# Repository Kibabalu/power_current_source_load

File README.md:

# power_current_source_load

power current source and load

A KiCad project.

The project consists of three PCBs: A general purpose power supply PCB, the control/supervise PCB and the main power PCB.

The power supply PCB gives a clean and stable +/- 15 V output voltage from a 'dirty' switching-mode power supply at its input. In detail it has the functions:
- inverse-polarity protection
- common mode disturbance filtering 
- low pass filtering with fg approx. 3 kHz (Pi-filter)
- low pass filtering with fg approx. 1.5 Hz (RC-Filter with capacitance multiplier)
- Voltage control of +/- 15 V, I_max approx. 1.5 A

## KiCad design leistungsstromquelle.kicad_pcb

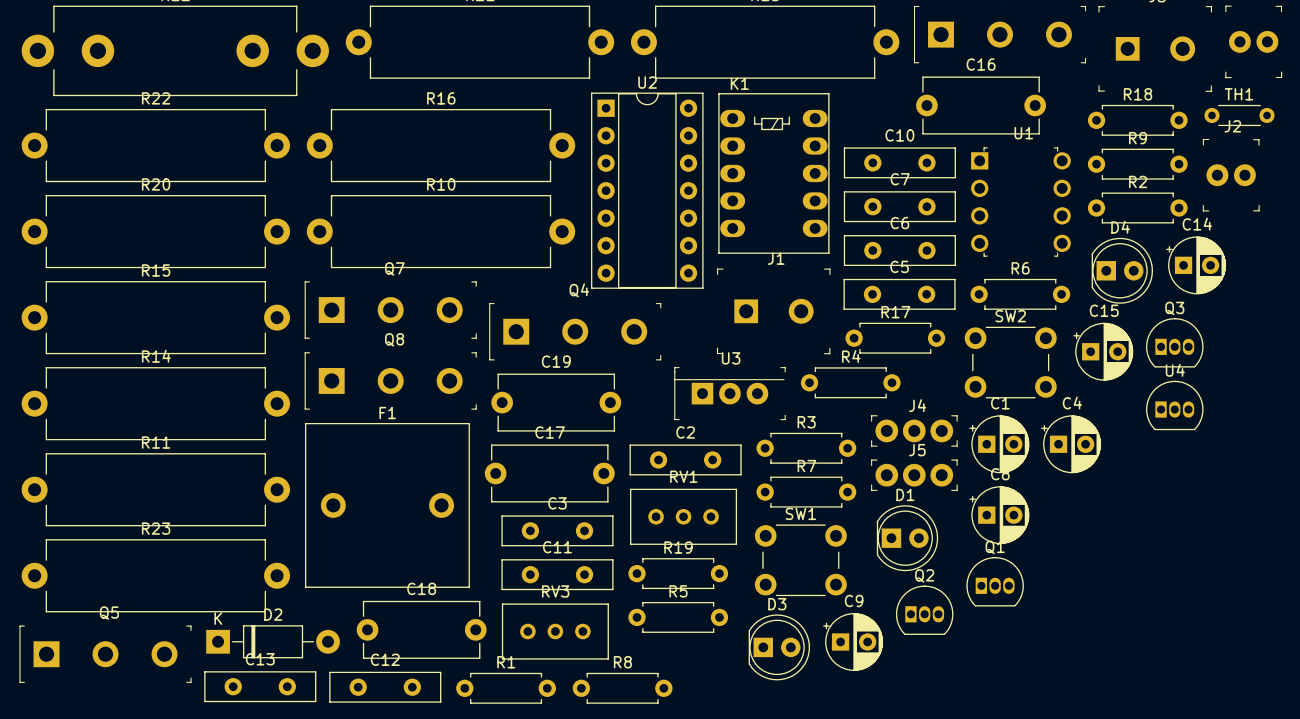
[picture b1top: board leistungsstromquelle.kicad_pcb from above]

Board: 2 copper layers, 71 parts (0 on the bottom side), 38 nets, no tracks yet.

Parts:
C1, C4, C8, C9, C14, C15: 1u; CP_Radial_D5.0mm_P2.50mm
C2, C5, C10, C11: 10n; C_Disc_D10.0mm_W2.5mm_P5.00mm
C3, C6, C12, C13: 100p; C_Disc_D10.0mm_W2.5mm_P5.00mm
C7: 22p; C_Disc_D10.0mm_W2.5mm_P5.00mm
C16, C17: 10n; C_Disc_D10.5mm_W5.0mm_P10.00mm
C18, C19: 100p; C_Disc_D10.5mm_W5.0mm_P10.00mm
D1, D3, D4: LED; LED_D5.0mm
D2: 1N4001; D_DO-41_SOD81_P10.16mm_Horizontal
F1: Fuse; Fuseholder_Cylinder-5x20mm_EATON_HBW_Vertical_Closed
J1, J3: OSTTC022162; Term_Block_1x2_P5.08MM
J2, J6: 640456-2; PinHeader_1x2_P2.54mm_Drill1.02mm
J4, J5: 640456-3; PinHeader_1x3_P2.54_Drill1.1mm
K1: FRT5_separated; Relay_DPDT_FRT5
Q1: BS250; TO-92_Inline
Q2, Q3: 2N7000; TO-92_Inline
Q4, Q5, Q6, Q7, Q8: TIP142; TO-247-3
R1, R2, R3, R7: 10k; R_Axial_DIN0207_L6.3mm_D2.5mm_P7.62mm_Horizontal
R4: 1Meg; R_Axial_DIN0207_L6.3mm_D2.5mm_P7.62mm_Horizontal
R5, R8: 1k5; R_Axial_DIN0207_L6.3mm_D2.5mm_P7.62mm_Horizontal
R6: 0; R_Axial_DIN0207_L6.3mm_D2.5mm_P7.62mm_Horizontal
R9: 90k; R_Axial_DIN0207_L6.3mm_D2.5mm_P7.62mm_Horizontal
R10, R11, R13, R14, R15, R16, R20, R21, R22, R23: 1; R_Axial_Power_L20.0mm_W6.4mm_P22.40mm
R12: 0.1; R_Axial_Shunt_L22.2mm_W8.0mm_PS14.30mm_P25.40mm
R17: 2k3; R_Axial_DIN0207_L6.3mm_D2.5mm_P7.62mm_Horizontal
R18, R19: 240; R_Axial_DIN0207_L6.3mm_D2.5mm_P7.62mm_Horizontal
RV1: 100k; Potentiometer_Bourns_3296W_Vertical
RV3: 2k; Potentiometer_Bourns_3296W_Vertical
SW1: SW_Push_Open; SW_PUSH_6mm_H5mm
SW2: SW_Push; SW_PUSH_6mm_H5mm
TH1: 100k; R_Axial_DIN0204_L3.6mm_D1.6mm_P5.08mm_Horizontal
U1: LM393; DIP-8_W7.62mm
U2: TL074; DIP-14_W7.62mm_Socket
U3: LM317T; TO-220-3
U4: LM317L_TO92; TO-92_Inline

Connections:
+5V: C15.1, C17.1, C19.1, R9.1, R19.1, U4.2
+12V: C1.1, C2.1, C3.1, C14.1, C16.1, C18.1, J6.2, Q1.3, R1.1, R5.1, R8.1, R18.1, TH1.2, U1.8, U3.2
GND: C1.2, C2.2, C3.2, C4.2, C5.2, C6.2, C8.2, C9.2, C10.2, C11.2, C12.2, C13.2, C14.2, C15.2, C16.2, C17.2, C18.2, C19.2, D3.1, J1.2, J2.2, J5.1, J6.1, K1.9, Q2.1, Q3.1, R2.2, R12.1, R12.2, R17.2, RV1.1, RV1.2, RV3.2, RV3.3, U1.4, U1.5, U2.11, U2.12
unnamed: C7.1, Q4.2, Q5.2, Q6.2, Q7.2, Q8.2, U2.8
unnamed: C7.2, R12.3, U2.9
unnamed: D1.2, R5.2
unnamed: D2.1, K1.1, K1.3, SW2.1
unnamed: D2.2, K1.10, R6.1
unnamed: D3.2, R6.2
unnamed: D4.1, Q2.3
unnamed: D4.2, R8.2
unnamed: F1.2, J1.1
unnamed: J2.1, R7.1
unnamed: J3.1, R12.4
unnamed: J3.2, R10.2, R11.2, R13.2, R14.2, R15.2, R16.2, R20.2, R21.2, R22.2, R23.2
unnamed: J4.1, J5.2
unnamed: J4.2, K1.7
unnamed: J4.3, R7.2
unnamed: J5.3, R9.2
unnamed: K1.4, SW1.1, SW2.2
unnamed: K1.8, Q3.3, U2.10
unnamed: Q1.1, SW1.2
unnamed: Q4.1, R10.1, R11.1
unnamed: Q5.1, R13.1, R14.1
unnamed: Q6.1, R15.1, R16.1
unnamed: Q7.1, R20.1, R21.1
unnamed: Q8.1, R22.1, R23.1
unnamed: R1.2, R2.1, U2.5
unnamed: R3.1, R4.2, U1.3
unnamed: R3.2, U2.1, U2.2
unnamed: R17.1, R18.2, U3.1
unnamed: R19.2, RV3.1, U4.1
unnamed: RV1.3, TH1.1, U2.3
unnamed: U1.2, U2.6, U2.7
unnamed: U1.6, U1.7
unnamed: U2.13, U2.14
VCC: C4.1, C5.1, C6.1, C8.1, C9.1, C10.1, C11.1, C12.1, C13.1, F1.1, Q4.3, Q5.3, Q6.3, Q7.3, Q8.3, U2.4, U3.3, U4.3
overtemp: D1.1, Q1.2, Q2.2, Q3.2, R4.1, U1.1

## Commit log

2020-06-05 1st commit
2020-06-05 readme
2020-06-06 minor changes
2020-06-06 structured
2020-06-06 minor change
2020-06-14 revision of Netzteil
2020-06-14 cleaning up
2020-06-28 change to SMD 1206 and restructuring
2020-06-28 file removed
2020-08-09 pcb netzteil rev. 1.0 finished
2020-08-09 file deleted
2020-08-09 readme edited
2020-08-24 photo added
